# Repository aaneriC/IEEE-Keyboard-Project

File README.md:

# IEEE-Keyboard-Project

This is a repository for our keyboard project, supported by IEEE at Cal Poly Pomona. In this repository contains our schematic and PCB design.

Authors: Matthew, Cassandra, Athan, Patrick, Cirena

Keybaord Layout:

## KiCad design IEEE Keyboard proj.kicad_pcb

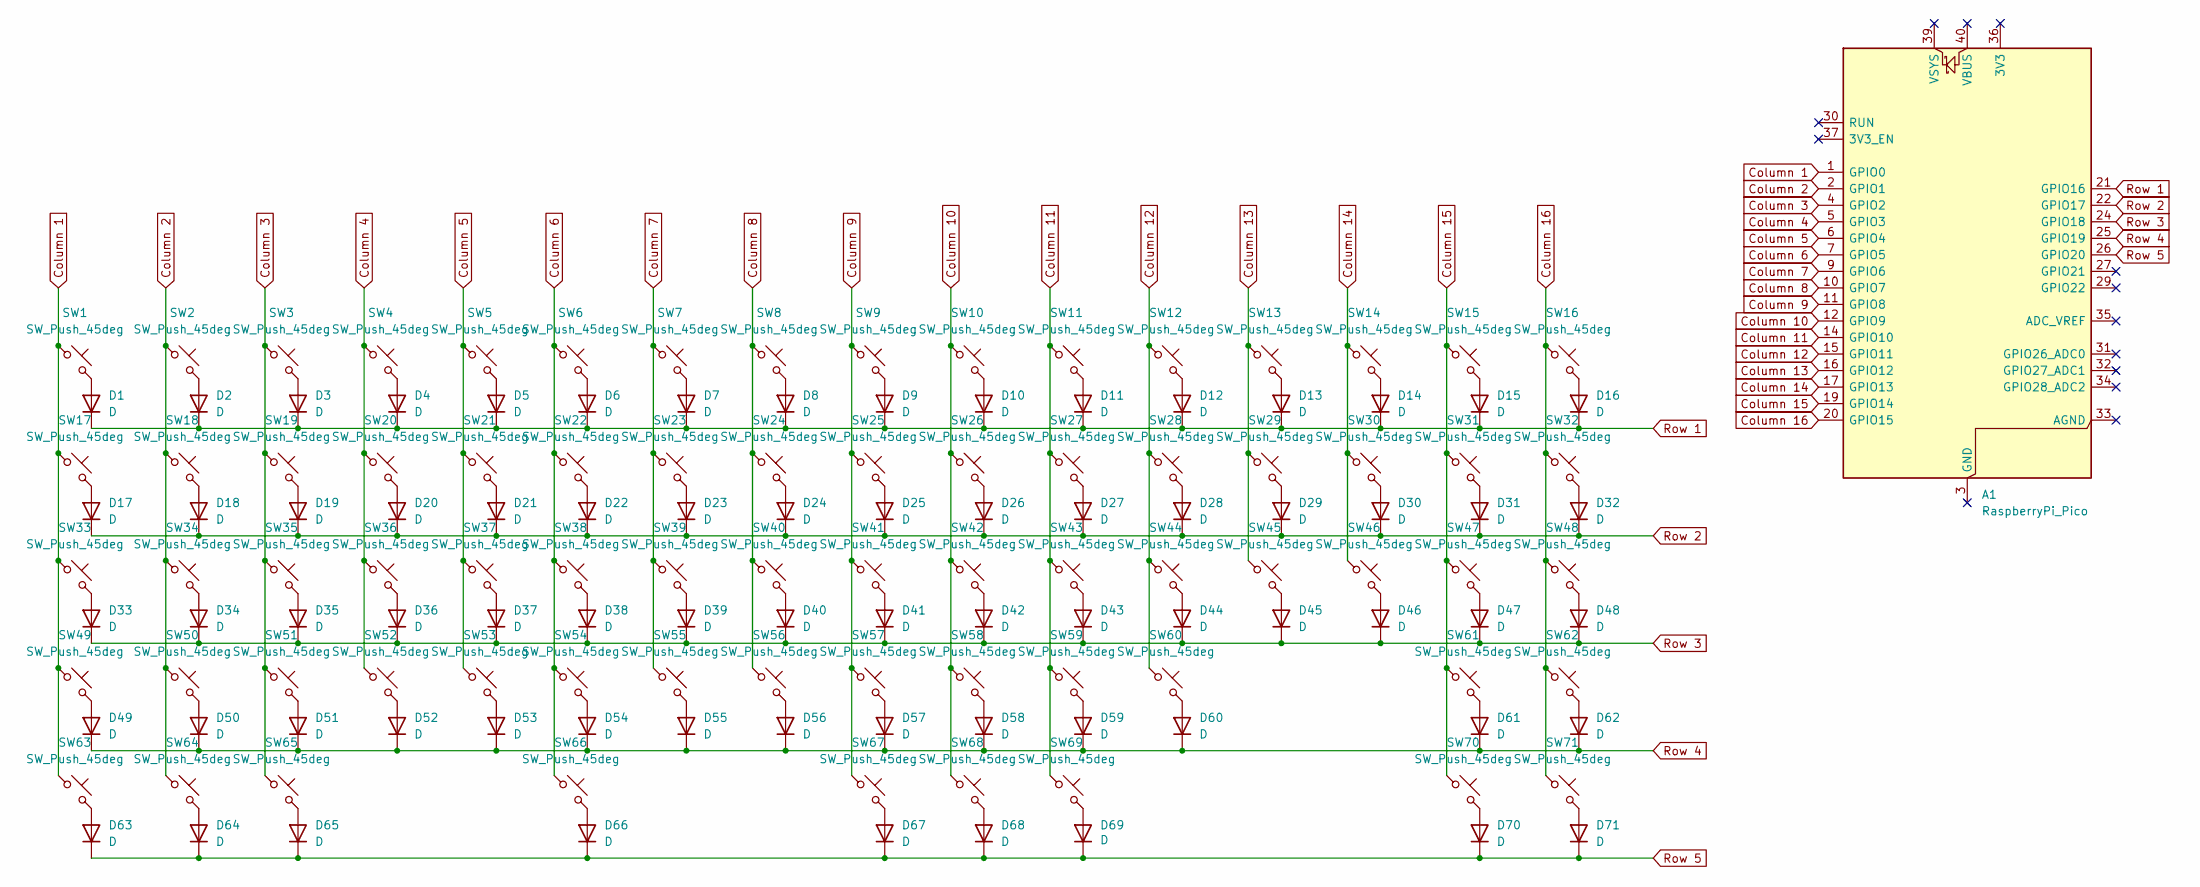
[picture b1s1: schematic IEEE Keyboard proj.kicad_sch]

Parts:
A1: RaspberryPi_Pico; RaspberryPi_Pico_Common_Unspecified
D1, D2, D3, D4, D5, D6, D7, D8, D9, D10, D11, D12, D13, D14, D15, D16, D17, D18, D19, D20, D21, D22, D23, D24, D25, D26, D27, D28, D29, D30, D31, D32, D33, D34, D35, D36, D37, D38, D39, D40, D41, D42, D43, D44, D45, D46, D47, D48, D49, D50, D51, D52, D53, D54, D55, D56, D57, D58, D59, D60, D61, D62, D63, D64, D65, D66, D67, D68, D69, D70, D71: D; D_DO-35_SOD27_P7.62mm_Horizontal
SW1, SW2, SW3, SW4, SW5, SW6, SW7, SW8, SW9, SW10, SW11, SW12, SW13, SW15, SW16, SW18, SW19, SW20, SW21, SW22, SW23, SW24, SW25, SW26, SW27, SW28, SW29, SW31, SW32, SW34, SW35, SW36, SW37, SW38, SW39, SW40, SW41, SW42, SW43, SW44, SW46, SW47, SW48, SW50, SW51, SW52, SW53, SW54, SW55, SW56, SW57, SW58, SW59, SW61, SW62, SW70, SW71: SW_Push_45deg; SW_MX_HS_CPG151101S11_1u
SW14: SW_Push_45deg; SW_Hotswap_Kailh_Choc_V1V2_2.00u
SW17: SW_Push_45deg; SW_MX_HS_CPG151101S11_1.5u
SW30: SW_Push_45deg; SW_Hotswap_Kailh_MX_1.50u
SW33: SW_Push_45deg; SW_MX_HS_CPG151101S11_1.75u
SW45, SW49: SW_Push_45deg; SW_Hotswap_Kailh_MX_2.25u
SW60: SW_Push_45deg; SW_Hotswap_Kailh_MX_2.75u
SW63, SW64, SW65, SW67, SW68, SW69: SW_Push_45deg; SW_Hotswap_Kailh_MX_1.25u
SW66: SW_Push_45deg; SW_Hotswap_Kailh_MX_6.25u

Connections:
Column 1: A1.1 (GPIO0), SW1.1, SW17.1, SW33.1, SW49.1, SW63.1
Column 2: A1.2 (GPIO1), SW2.1, SW18.1, SW34.1, SW50.1, SW64.1
Column 3: A1.4 (GPIO2), SW3.1, SW19.1, SW35.1, SW51.1, SW65.1
Column 4: A1.5 (GPIO3), SW4.1, SW20.1, SW36.1, SW52.1
Column 5: A1.6 (GPIO4), SW5.1, SW21.1, SW37.1, SW53.1
Column 6: A1.7 (GPIO5), SW6.1, SW22.1, SW38.1, SW54.1, SW66.1
Column 7: A1.9 (GPIO6), SW7.1, SW23.1, SW39.1, SW55.1
Column 8: A1.10 (GPIO7), SW8.1, SW24.1, SW40.1, SW56.1
Column 9: A1.11 (GPIO8), SW9.1, SW25.1, SW41.1, SW57.1, SW67.1
Column 10: A1.12 (GPIO9), SW10.1, SW26.1, SW42.1, SW58.1, SW68.1
Column 11: A1.14 (GPIO10), SW11.1, SW27.1, SW43.1, SW59.1, SW69.1
Column 12: A1.15 (GPIO11), SW12.1, SW28.1, SW44.1, SW60.1
Column 13: A1.16 (GPIO12), SW13.1, SW29.1, SW45.1
Column 14: A1.17 (GPIO13), SW14.1, SW30.1, SW46.1
Column 15: A1.19 (GPIO14), SW15.1, SW31.1, SW47.1, SW61.1, SW70.1
Column 16: A1.20 (GPIO15), SW16.1, SW32.1, SW48.1, SW62.1, SW71.1
unnamed: D1.2 (A), SW1.2
unnamed: D2.2 (A), SW2.2
unnamed: D3.2 (A), SW3.2
unnamed: D4.2 (A), SW4.2
unnamed: D5.2 (A), SW5.2
unnamed: D6.2 (A), SW6.2
unnamed: D7.2 (A), SW7.2
unnamed: D8.2 (A), SW8.2
unnamed: D9.2 (A), SW9.2
unnamed: D10.2 (A), SW10.2
unnamed: D11.2 (A), SW11.2
unnamed: D12.2 (A), SW12.2
unnamed: D13.2 (A), SW13.2
unnamed: D14.2 (A), SW14.2
unnamed: D15.2 (A), SW15.2
unnamed: D16.2 (A), SW16.2
unnamed: D17.2 (A), SW17.2
unnamed: D18.2 (A), SW18.2
unnamed: D19.2 (A), SW19.2
unnamed: D20.2 (A), SW20.2
unnamed: D21.2 (A), SW21.2
unnamed: D22.2 (A), SW22.2
unnamed: D23.2 (A), SW23.2
unnamed: D24.2 (A), SW24.2
unnamed: D25.2 (A), SW25.2
unnamed: D26.2 (A), SW26.2
unnamed: D27.2 (A), SW27.2
unnamed: D28.2 (A), SW28.2
unnamed: D29.2 (A), SW29.2
unnamed: D30.2 (A), SW30.2
unnamed: D31.2 (A), SW31.2
unnamed: D32.2 (A), SW32.2
unnamed: D33.2 (A), SW33.2
unnamed: D34.2 (A), SW34.2
unnamed: D35.2 (A), SW35.2
unnamed: D36.2 (A), SW36.2
unnamed: D37.2 (A), SW37.2
unnamed: D38.2 (A), SW38.2
unnamed: D39.2 (A), SW39.2
unnamed: D40.2 (A), SW40.2
unnamed: D41.2 (A), SW41.2
unnamed: D42.2 (A), SW42.2
unnamed: D43.2 (A), SW43.2
unnamed: D44.2 (A), SW44.2
unnamed: D45.2 (A), SW45.2
unnamed: D46.2 (A), SW46.2
unnamed: D47.2 (A), SW47.2
unnamed: D48.2 (A), SW48.2
unnamed: D49.2 (A), SW49.2
unnamed: D50.2 (A), SW50.2
unnamed: D51.2 (A), SW51.2
unnamed: D52.2 (A), SW52.2
unnamed: D53.2 (A), SW53.2
unnamed: D54.2 (A), SW54.2
unnamed: D55.2 (A), SW55.2
unnamed: D56.2 (A), SW56.2
unnamed: D57.2 (A), SW57.2
unnamed: D58.2 (A), SW58.2
unnamed: D59.2 (A), SW59.2
unnamed: D60.2 (A), SW60.2
unnamed: D61.2 (A), SW61.2
unnamed: D62.2 (A), SW62.2
unnamed: D63.2 (A), SW63.2
unnamed: D64.2 (A), SW64.2
unnamed: D65.2 (A), SW65.2
unnamed: D66.2 (A), SW66.2
unnamed: D67.2 (A), SW67.2
unnamed: D68.2 (A), SW68.2
unnamed: D69.2 (A), SW69.2
unnamed: D70.2 (A), SW70.2
unnamed: D71.2 (A), SW71.2
Row 1: A1.21 (GPIO16), D1.1 (K), D2.1 (K), D3.1 (K), D4.1 (K), D5.1 (K), D6.1 (K), D7.1 (K), D8.1 (K), D9.1 (K), D10.1 (K), D11.1 (K), D12.1 (K), D13.1 (K), D14.1 (K), D15.1 (K), D16.1 (K)
Row 2: A1.22 (GPIO17), D17.1 (K), D18.1 (K), D19.1 (K), D20.1 (K), D21.1 (K), D22.1 (K), D23.1 (K), D24.1 (K), D25.1 (K), D26.1 (K), D27.1 (K), D28.1 (K), D29.1 (K), D30.1 (K), D31.1 (K), D32.1 (K)
Row 3: A1.24 (GPIO18), D33.1 (K), D34.1 (K), D35.1 (K), D36.1 (K), D37.1 (K), D38.1 (K), D39.1 (K), D40.1 (K), D41.1 (K), D42.1 (K), D43.1 (K), D44.1 (K), D45.1 (K), D46.1 (K), D47.1 (K), D48.1 (K)
Row 4: A1.25 (GPIO19), D49.1 (K), D50.1 (K), D51.1 (K), D52.1 (K), D53.1 (K), D54.1 (K), D55.1 (K), D56.1 (K), D57.1 (K), D58.1 (K), D59.1 (K), D60.1 (K), D61.1 (K), D62.1 (K)
Row 5: A1.26 (GPIO20), D63.1 (K), D64.1 (K), D65.1 (K), D66.1 (K), D67.1 (K), D68.1 (K), D69.1 (K), D70.1 (K), D71.1 (K)

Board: 2 copper layers, 143 parts (0 on the bottom side), 92 nets, no tracks yet.

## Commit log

2026-03-11 Created list
2026-03-11 Enhance README with project details and authors
    Added project description and authors to README.
2026-03-11 Update MCU to Devboard: RaspberryPi Pico in Footprintlist
2026-03-11 Create tempfile
2026-03-11 Added datasheet for Raspberry Pi Pico Devboard
2026-03-11 Add keyboard layout image to README
2026-03-12 Add PCB file
2026-03-12 Added updated schematic
2026-03-18 keyboard schem and PCB
2026-03-18 uploaded most recent version of project
2026-03-25 Placed diodes, added some traces
2026-03-26 Add files via upload
    Finished the traces and added stabilizers
2026-04-02 Added recent project files
2026-04-22 Add .dxf file for CAD
2026-04-22 add cad plate drawing
2026-04-22 Add SolidWorks Plate
2026-04-22 Add files via upload
    fixed switches
2026-04-30 Added Final revision
